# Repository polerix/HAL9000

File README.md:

# HAL 9000 Viewscreen

Life-size HAL 9000 replica display system. A Pygame kiosk app drives a 7" 1024×600 HDMI display in portrait orientation (600×1024), cycling through 12 spacecraft systems every 30 seconds and showing two panels per system:

- **High Screen** – Red function label panel with the active system code (e.g. `ATM`, `NAV`, `DMG`)
- **Lower Screen** – Looping video animation matching the current function

Primary deployment target is a Raspberry Pi 3 driving the physical prop display — see [`RaspberryPi 3.md`](RaspberryPi%203.md) for hardware wiring, HDMI/portrait config, and the systemd service. This README covers running and developing the app, including on a desktop (macOS/Linux) for testing.

## Requirements

- Python 3.10+
- [`pygame-ce`](https://pyga.me/) (community fork of pygame — see note below)

Dependencies are pinned in [`requirements.txt`](requirements.txt).

> **Why pygame-ce, not pygame:** `pygame` 2.6.1 has a circular-import bug in `pygame.font` on newer Python releases (confirmed on 3.14), which crashes the app on startup with `NotImplementedError: font module not available`. `pygame-ce` is an actively maintained, drop-in-compatible fork without that bug. If you're on an older/stable Python and prefer upstream `pygame`, it should still work — just swap the pin in `requirements.txt`.

## Quick Start (Desktop / macOS testing)

Use a virtual environment so nothing touches your system Python:

```bash
cd HAL9000
python3 -m venv .venv
source .venv/bin/activate
pip install -r requirements.txt

python3 hal_viewscreen.py --windowed   # windowed, for testing
python3 hal_viewscreen.py              # fullscreen
```

`.venv/` is self-ignored by git (venvs created with `python -m venv` write their own `.gitignore`), so it never needs to be committed.

## Quick Start (Raspberry Pi 3, production)

```bash
git clone <repo-url> ~/HAL9000
cd ~/HAL9000
chmod +x setup_pi.sh
sudo ./setup_pi.sh
sudo reboot
```

Full hardware setup, HDMI portrait config, and systemd service management: see [`RaspberryPi 3.md`](RaspberryPi%203.md).

## Keyboard Controls (Testing)

| Key | Action |
|---|---|
| `→` Right Arrow | Next function |
| `←` Left Arrow | Previous function |
| `Space` | Resume auto-cycling |
| `Esc` | Quit |

## System Functions

| Code | System | Subtitle |
|---|---|---|
| ATM | Spacecraft Atmosphere Monitoring | O2N: 14-RA |
| CNT | Control | SYS: 09-MX |
| COM | Communications | FRQ: 31-AE |
| DMG | System Damage | GPM: 72-KC |
| FLX | Flight Dynamics | DYN: 58-PL |
| GDE | Guidance Data Extension | NAV: 43-QR |
| HIB | Hibernation | CRY: 06-TB |
| LIF | Life Support | ENV: 21-SG |
| MEM | Memory | BNK: 88-FH |
| NAV | Navigation | TRJ: 55-WD |
| NUC | Nuclear Reactor Status | RCT: 37-JN |
| VEH | Vehicle Status | HUL: 64-BV |

## Architecture

```
hal_viewscreen.py      Main application (Pygame)
├── config.py          Constants, layout, function definitions
├── Video/             MP4 animations (7-8 per function)
├── Fonts/             Eurostile KFB font family
└── Artwork/SVG/       Screen layout + example panel
```

## Files

| File | Purpose |
|---|---|
| `hal_viewscreen.py` | Main display application |
| `config.py` | Configuration & constants |
| `requirements.txt` | Python dependencies |
| `setup_pi.sh` | Raspberry Pi setup script |
| `hal9000-viewscreen.service` | Systemd auto-start unit (Pi) |
| `RaspberryPi 3.md` | Hardware setup & Pi deployment reference |
| `7" ScreenSpecifications.md` | Display hardware spec sheet |

## Notes

- Video playback is fully in-window: frames are decoded with OpenCV and drawn directly onto the same pygame surface as the rest of the UI, rather than shelling out to an external player. There is no separate OS-level video window to position — the whole display is one window.
- This is software decoding. See [`RaspberryPi 3.md`](RaspberryPi%203.md) for a note on Pi 3 performance if you deploy there.
- The `set_function()` API in `FunctionController` is ready for external control (Arduino serial, network, etc.)
- Cycle interval is configurable in `config.py` (`CYCLE_INTERVAL_SEC`)
- Font rendering uses Eurostile KFB Bold Extended (matching the movie prop typography)

## Licensing

The source code in this repository is released under the [MIT License](LICENSE).

Third-party material bundled in this repository (fonts, audio, video, artwork, saved web pages and similar files) is **not** covered by that license. It remains the property of its respective owners and is included under their own terms. If you are a rights holder and want something removed, please open an issue.

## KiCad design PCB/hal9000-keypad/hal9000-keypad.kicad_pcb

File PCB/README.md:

# HAL 9000 Keypad PCB

10-button backlit keypad for the HAL 9000 terminal. Connects to a Vasiumic MCP23017 I2C GPIO expander via Dupont wires.

## Specs
- Board: 75.10 × 30.20 mm, 2-layer
- Buttons: 6×6×5mm momentary tactile, 4-pin DIP, 15mm pitch (2×5 grid)
- LEDs: 5mm through-hole, always-on, one per button in function color
- Resistors: current-limiting per LED color (330Ω red, 270Ω green, 180Ω blue, 300Ω amber)
- J1: 10-pin 2.54mm Dupont → MCP23017 GPA0–7 + GPB0–1
- J2: 2-pin power (5V + GND)

## Button Layout (row × col)
| | Col 1 | Col 2 | Col 3 | Col 4 | Col 5 |
|---|---|---|---|---|---|
| Row 1 | HIB | LIF | COM | NAV | MEM |
| Row 2 | ATM | FLX | NUC | WEA | MED |

## Files
- `hal9000-keypad/` — KiCad project (.kicad_sch, .kicad_pcb, .kicad_pro)
- `hal9000-keypad-pcb.zip` — full project archive for peer review
- `author-hal9000-keypad.mjs` — MCP authoring script that generated this design

## Notes
Resistors may need manual placement adjustment in KiCad PCB editor to clear courtyard overlaps (all nets and footprints are correct).

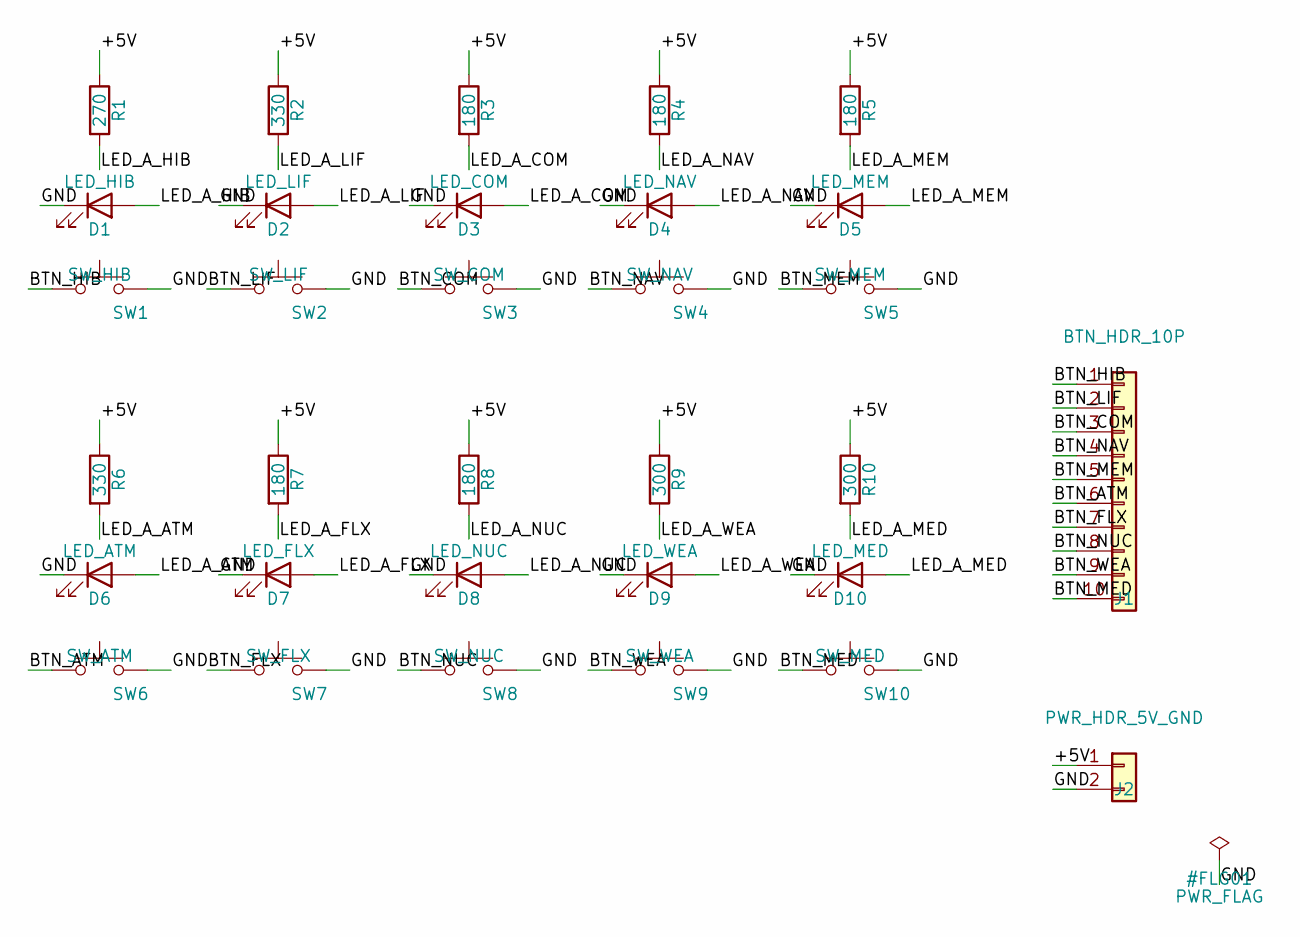
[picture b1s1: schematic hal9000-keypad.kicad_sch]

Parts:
D1: LED_HIB; LED_D5.0mm
D2: LED_LIF; LED_D5.0mm
D3: LED_COM; LED_D5.0mm
D4: LED_NAV; LED_D5.0mm
D5: LED_MEM; LED_D5.0mm
D6: LED_ATM; LED_D5.0mm
D7: LED_FLX; LED_D5.0mm
D8: LED_NUC; LED_D5.0mm
D9: LED_WEA; LED_D5.0mm
D10: LED_MED; LED_D5.0mm
J1: BTN_HDR_10P; PinHeader_1x10_P2.54mm_Vertical
J2: PWR_HDR_5V_GND; PinHeader_1x02_P2.54mm_Vertical
R1: 270; R_Axial_DIN0207_L6.3mm_D2.5mm_P10.16mm_Horizontal
R2, R6: 330; R_Axial_DIN0207_L6.3mm_D2.5mm_P10.16mm_Horizontal
R3, R4, R5, R7, R8: 180; R_Axial_DIN0207_L6.3mm_D2.5mm_P10.16mm_Horizontal
R9, R10: 300; R_Axial_DIN0207_L6.3mm_D2.5mm_P10.16mm_Horizontal
SW1: SW_HIB; SW_PUSH_6mm
SW2: SW_LIF; SW_PUSH_6mm
SW3: SW_COM; SW_PUSH_6mm
SW4: SW_NAV; SW_PUSH_6mm
SW5: SW_MEM; SW_PUSH_6mm
SW6: SW_ATM; SW_PUSH_6mm
SW7: SW_FLX; SW_PUSH_6mm
SW8: SW_NUC; SW_PUSH_6mm
SW9: SW_WEA; SW_PUSH_6mm
SW10: SW_MED; SW_PUSH_6mm

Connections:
+5V: J2.1, R1.1, R2.1, R3.1, R4.1, R5.1, R6.1, R7.1, R8.1, R9.1, R10.1
BTN_ATM: J1.6, SW6.1
BTN_COM: J1.3, SW3.1
BTN_FLX: J1.7, SW7.1
BTN_HIB: J1.1, SW1.1
BTN_LIF: J1.2, SW2.1
BTN_MED: J1.10, SW10.1
BTN_MEM: J1.5, SW5.1
BTN_NAV: J1.4, SW4.1
BTN_NUC: J1.8, SW8.1
BTN_WEA: J1.9, SW9.1
GND: D1.1 (K), D2.1 (K), D3.1 (K), D4.1 (K), D5.1 (K), D6.1 (K), D7.1 (K), D8.1 (K), D9.1 (K), D10.1 (K), J2.2, SW1.2, SW2.2, SW3.2, SW4.2, SW5.2, SW6.2, SW7.2, SW8.2, SW9.2, SW10.2
LED_A_ATM: D6.2 (A), R6.2
LED_A_COM: D3.2 (A), R3.2
LED_A_FLX: D7.2 (A), R7.2
LED_A_HIB: D1.2 (A), R1.2
LED_A_LIF: D2.2 (A), R2.2
LED_A_MED: D10.2 (A), R10.2
LED_A_MEM: D5.2 (A), R5.2
LED_A_NAV: D4.2 (A), R4.2
LED_A_NUC: D8.2 (A), R8.2
LED_A_WEA: D9.2 (A), R9.2

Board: 2 copper layers, 32 parts (0 on the bottom side), 22 nets, no tracks yet.
